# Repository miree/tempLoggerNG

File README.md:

# tempLoggerNG

A four-channel PT-100 temperature logging device built around a Texas
Instruments ADS1248 precision delta-sigma ADC and an ATmega328p
microcontroller with V-USB (software-only USB, no dedicated USB
controller chip). The device connects directly to a PC over USB and is
controlled by a small command-line tool that triggers measurements and
logs resistance/temperature readings to a file.

https://emsyfs.blogspot.com/2017/07/pt-100-temperature-logger.html

## Features

- 4 independent PT-100 RTD input channels, read via a single ADS1248
  24-bit ADC using its internal multiplexer and a programmable current
  source (IDAC) to excite each sensor.
- Full 4-wire measurement on all 4 channels, eliminating lead
  resistance errors for accurate readings even with long sensor
  cables.
- On-board diode temperature sensor, used to compensate for
  temperature drift of the measurement electronics themselves.
- Linear temperature-compensation coefficients (`a`, `b`) stored in the
  ATmega's EEPROM, so each device can be individually calibrated and
  keeps its calibration across power cycles.
- USB connectivity without a dedicated USB interface chip, using the
  V-USB software USB implementation on the ATmega328p.
- A command-line host tool (`templogger`) that:
  - reads out the 4 channels at a configurable sample rate,
  - converts raw resistance to temperature using the Callendar-Van
    Dusen equation for PT-100 sensors,
  - logs readings (time, diode voltage, and temperature or resistance
    per channel) to a plain-text data file,
  - optionally applies/updates the temperature-compensation
    calibration,
  - can read/write individual ADS1248 configuration registers for
    debugging, and
  - includes a USB round-trip echo self-test.
- Full KiCad hardware design (schematic, PCB layout, custom
  footprints, Specctra autorouter export, and a rendered schematic
  PDF) for building the device yourself.

## Repository layout

```
firmware/     ATmega328p firmware (C), including the V-USB driver and
              the ADS1248 driver
commandline/  Host-side command-line tool ("templogger") using libusb
hardware/     KiCad schematic/PCB project, footprints, and a PDF of
              the schematic
```

## Hardware

The design files live in `hardware/` as a KiCad project
(`tempLoggerNG.pro`, `tempLoggerNG.sch`, `tempLoggerNG.kicad_pcb`). A
rendered PDF of the schematic is included as
`tempLoggerNG-schematic.pdf` if you just want to look at the circuit
without opening KiCad.

> **Note:** This project was originally designed in an older version
> of KiCad (legacy schematic/library format). Opening it in a modern
> KiCad release will likely trigger the automatic "symbol rescue"
> feature, which copies any symbols it can't resolve against current
> libraries into local rescue files. This is expected and does not
> modify the original schematic; if KiCad has already run through
> this once in your checkout, you may need to clean up before
> committing anything.

## Firmware

The firmware lives in `firmware/` and is built with `avr-gcc` for the
ATmega328p.

### Requirements

- `avr-gcc` / `avr-libc` (AVR toolchain)
- `avrdude`
- An AVR ISP programmer, such as a USBasp (the Makefile defaults to
  `avrdude -c usbasp -p m328p` — edit `firmware/Makefile` if you use a
  different programmer)

### Build and flash

```sh
cd firmware
make          # builds main.hex
make flash    # flashes main.hex to the ATmega328p via avrdude/usbasp
```

The ATmega328p is clocked at 12 MHz (`F_CPU`, set in `main.c` and the
Makefile) and must be fused accordingly (external crystal, no
clock-divide) before flashing application code — the fuse bytes are
not set by this Makefile and must be programmed separately with
`avrdude`, matching whatever oscillator is fitted on your board.

Other useful targets:

```sh
make disasm   # disassemble main.bin with avr-objdump
make clean    # remove build artifacts
```

The firmware never leave debug output enabled in a flashed device —
the comment in the Makefile is explicit that debug builds distort the
timing the USB stack depends on.

## Command-line tool

The host tool lives in `commandline/` and talks to the device over USB
using libusb (the classic 0.1 API, via `libusb-config`).

### Requirements

- `gcc`
- `libusb` (0.1, providing `libusb-config`)

### Build

```sh
cd commandline
make
```

This produces a `templogger` binary. The device identifies itself
over USB using obdev's free shared VID/PID (`0x16C0`/`0x05DC`) with
manufacturer string `www.obdev.at` and product string `Temp-Logger`,
so no special udev rule beyond generic USB access permissions is
normally required — just make sure your user can access the USB
device (e.g. via a udev rule granting access for that VID/PID, or by
running as root).

### Usage

```
usage: ./templogger [ch1] [ch2] [ch3] [ch4] [all] [options]
```

Specify which channel(s) to log with one or more of `ch1`, `ch2`,
`ch3`, `ch4`, or `all`.

Options:

```
 -v          : verbose
 -q          : quiet
 -o filename : name of data file. default is "temperature.dat"
 -N n        : stop measurement after n samples
 -t t        : stop measurement after t seconds
 -d delta    : take a sample every delta seconds. Default is 0.5, min is 0.15
 -r          : read registers (for debugging purposes)
 -h          : output this help
```

Example — log channels 1 and 2 to `run1.dat`, once per second, for 60
samples:

```sh
./templogger ch1 ch2 -o run1.dat -d 1 -N 60
```

### Calibration procedure

Each device's on-board diode-based temperature compensation uses two
coefficients, `a` and `b`, such that:

```
R_comp = a - b * V_diode
R      = R_measured - R_comp
```

To determine and store them for a given device:

1. Connect a fixed, known resistor (e.g. 100 Ω) in place of a sensor.
2. Disable temperature compensation with `-x` and log resistance
   directly with `-R`.
3. Heat up the device itself (not the resistor) and record data while
   it cools down.
4. Plot `V_diode` against `R_measured - 100 Ω` and fit a straight line
   to obtain `a` and `b`.
5. Write the coefficients to the device's EEPROM:
   ```sh
   ./templogger -c <a> <b>
   ```

Once written, the coefficients are read back from EEPROM
automatically and applied during normal logging unless `-x` is given.

### Self-test

```sh
./templogger test
```

Sends 1000 random values to the device and checks that they are
echoed back correctly, as a basic USB communication sanity check.

## License

The firmware and command-line tool (`firmware/`, `commandline/`) are
licensed under the GNU General Public License v2 (see `LICENSE`). The
bundled V-USB driver (`firmware/usbdrv/`) is dual-licensed under GPLv2
or a commercial license from Objective Development — see
`firmware/usbdrv/License.txt` and
`firmware/usbdrv/CommercialLicense.txt` for details, and
`firmware/usbdrv/USB-ID-FAQ.txt` / `USB-IDs-for-free.txt` regarding use
of the shared VID/PID.

The hardware design (`hardware/`) is licensed under the CERN Open
Hardware Licence Version 2 - Strongly Reciprocal (CERN-OHL-S v2), see
`LICENSE-HARDWARE`.

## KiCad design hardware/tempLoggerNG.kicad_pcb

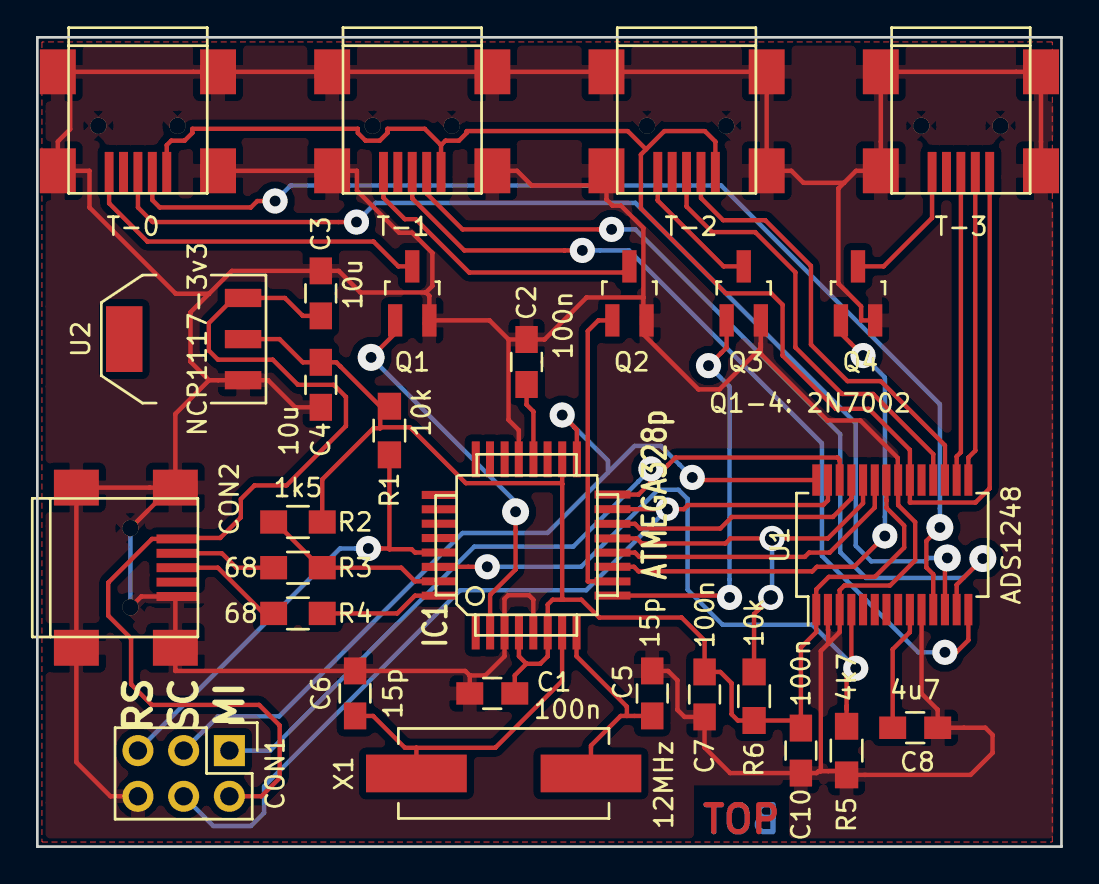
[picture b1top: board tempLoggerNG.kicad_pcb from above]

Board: 2 copper layers, 56.9 x 45.0 mm, 29 parts (0 on the bottom side), 36 nets.

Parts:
C1, C2, C7, C10: 100n; C_0805_HandSoldering
C3, C4: 10u; C_0805_HandSoldering
C5, C6: 15p; C_0805_HandSoldering
C8: 4u7; C_0805_HandSoldering
CON1: MR-AVR-ISP-6; Pin_Header_Straight_2x03
CON2: USB-MINI-B; USB_Mini-B
IC1: ATMEGA328p; TQFP32
Q1, Q2, Q3: MOS_N; SOT-23_GSD_Handsoldering
Q4: Q1-4: 2N7002; SOT-23_GSD_Handsoldering
R1, R6: 10k; R_0805_HandSoldering
R2: 1k5; R_0805_HandSoldering
R3, R4: 68; R_0805_HandSoldering
R5: 4k7; R_0805_HandSoldering
T-0, T-1, T-2, T-3: USB-MINI-B; USB_Mini-B
U1: ADS1248; SSOP-28_5.3x10.2mm_Pitch0.65mm
U2: NCP1117-3v3; SOT-223
X1: 12MHz; Crystal_HC49-SD_SMD

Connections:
+3.3V: C1.1, C4.1, C7.1, C10.2, IC1.4, IC1.6, IC1.18, R1.1, R2.1, R6.1, U1.1, U1.22, U2.2
+5V: C3.1, CON1.2, CON2.1, U2.3
/ADS_CS: IC1.13, R6.2, U1.24
/ADS_DIN: CON1.4, IC1.15, U1.27
/ADS_DOUT: CON1.1, IC1.16, U1.26
/ADS_DRDY: IC1.14, U1.25
/ADS_RESET: IC1.30, R5.1, U1.4
/ADS_SCLK: CON1.3, IC1.17, U1.28
/ADS_START: IC1.12, U1.23
/AVR_D+: IC1.32, R4.2
/AVR_D-: IC1.31, R2.2, R3.2
/AVR_RESET: CON1.5, IC1.29, R1.2
/D+: CON2.3, R4.1
/D-: CON2.2, R3.1
/XTAL1: C6.1, IC1.7, X1.2
/XTAL2: C5.1, IC1.8, X1.1
/ch01_activate: IC1.2, Q1.G
/ch23_activate: IC1.9, Q3.G
/ch45_activate: IC1.10, Q2.G
/ch67_activate: IC1.11, Q4.G
GND: C1.2, C2.2, C3.2, C4.2, C5.2, C6.2, C7.2, C8.1, C10.1, CON1.6, CON2.5, CON2.6, CON2.7, CON2.8, CON2.9, IC1.3, IC1.5, IC1.21, Q1.S, Q2.S, Q3.S, Q4.S, R5.2, T-0.6, T-0.7, T-0.8, T-0.9, T-1.6, T-1.7, T-1.8, T-1.9, T-2.6, T-2.7, T-2.8, T-2.9, T-3.6, T-3.7, T-3.8, T-3.9, U1.2, U1.3, U1.10, U1.21, U2.1
unnamed: C2.1, IC1.20
unnamed: C8.2, U1.9
unnamed: T-0.1, T-1.1, T-2.1, T-3.1, U1.20
unnamed: T-0.2, U1.11
unnamed: T-0.3, U1.12
unnamed: Q1.D, T-0.5
unnamed: T-1.2, U1.13
unnamed: T-1.3, U1.14
unnamed: Q2.D, T-1.5
unnamed: T-2.2, U1.17
unnamed: T-2.3, U1.18
unnamed: Q3.D, T-2.5
unnamed: T-3.2, U1.15
unnamed: T-3.3, U1.16
unnamed: Q4.D, T-3.5

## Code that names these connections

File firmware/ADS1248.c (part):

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void ADS_init()
{
	// set the AVR-DDR registers to correct input/output 
	ADS_DDR_START  |=  (1<<ADS_P_START);   // ADS_START pin is AVR-output
	ADS_DDR_CS     |=  (1<<ADS_P_CS);      // ADS_CS    pin is AVR-output
	ADS_DDR_DRDY   &= ~(1<<ADS_P_DRDY);    // ADS_DRDY  pin is AVR-input
	ADS_DDR_DIN    |=  (1<<ADS_P_DIN);     // ADS_DIN   pin is AVR-output
	ADS_DDR_DOUT   &= ~(1<<ADS_P_DOUT);    // ADS_DOUT  pin is AVR-input
	ADS_DDR_SCLK   |=  (1<<ADS_P_SCLK);    // ADS_SCLK  pin is AVR-output
	ADS_DDR_RESET  |=  (1<<ADS_P_RESET);   // ADS_RESET pin is AVR-output
	
	ADS_PORT_START &= ~(1<<ADS_P_START);   // pull ADS_START pin low  
	ADS_PORT_RESET &= ~(1<<ADS_P_RESET);   // pull ADS_RESET pin low  (active reset of ADS chip)
	ADS_PORT_CS    |=  (1<<ADS_P_CS);      // pull ADS_CS pin high     (disable serial SPI communication)
	ADS_PORT_SCLK  &= ~(1<<ADS_P_SCLK);    // pull ADS_SCLK pin low   (default state for clock pin)
	ADS_PORT_RESET |=  (1<<ADS_P_RESET);   // pull ADS_RESET pin high (release the reset condition)
	
	// set the AVR-DDR registers for the current selection MOSFETs 
	ADS_DDR_MOS01 |=  (1<<ADS_P_MOS01);
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
void ADS_start()
{
	ADS_PORT_START |=  (1<<ADS_P_START);   // pull ADS_START pin high
}

void ADS_stop()
{
	ADS_PORT_START &= ~(1<<ADS_P_START);   // pull ADS_START pin low
}
void ADS_start_pulse()
{
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	ADS_start();
	// pull SCLK pin up and down. For some reason the 
	//   hardware SPI interface only after doing this.
	ADS_PORT_SCLK  |=  (1<<ADS_P_SCLK);    // pull ADS_SCLK pin high (default state for clock pin)
	ADS_PORT_SCLK  &= ~(1<<ADS_P_SCLK);    // pull ADS_SCLK pin low  (default state for clock pin)

	// activate the SPI interface of the ADS device
	ADS_PORT_CS    &= ~(1<<ADS_P_CS);      // pull ADS_CS pin low (activate SPI interface)
}

uint8_t ADS_SPI_transmit(uint8_t cData)
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
void ADS_SPI_stop()
{
	ADS_PORT_CS    |=  (1<<ADS_P_CS);      // pull ADS_CS pin low (activate SPI interface)
	//ADS_PORT_SCLK  &= ~(1<<ADS_P_SCLK);    // pull ADS_SCLK pin low (default state for clock pin)
	ADS_stop();
}

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
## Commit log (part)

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2016-06-30 adding files
2016-06-30 fixed wrong Makefile dependence
2016-06-30 added missing KiCad file
2016-06-30 made copper layers visible
2016-06-30 fix warnings in cmopilation of commandline application
2016-06-30 fixed a comment
2016-06-30 added pdf schematic
2016-07-19 commandline tool can show detailed register content
2016-07-19 changed product name in error message of commandline tool
2017-07-01 add linear temperature compensation coefficients that are stored in eeprom
2017-07-01 cleanup and completing help output
2017-07-06 commandline: limit readout rate to 0.15 to be on the safe side
